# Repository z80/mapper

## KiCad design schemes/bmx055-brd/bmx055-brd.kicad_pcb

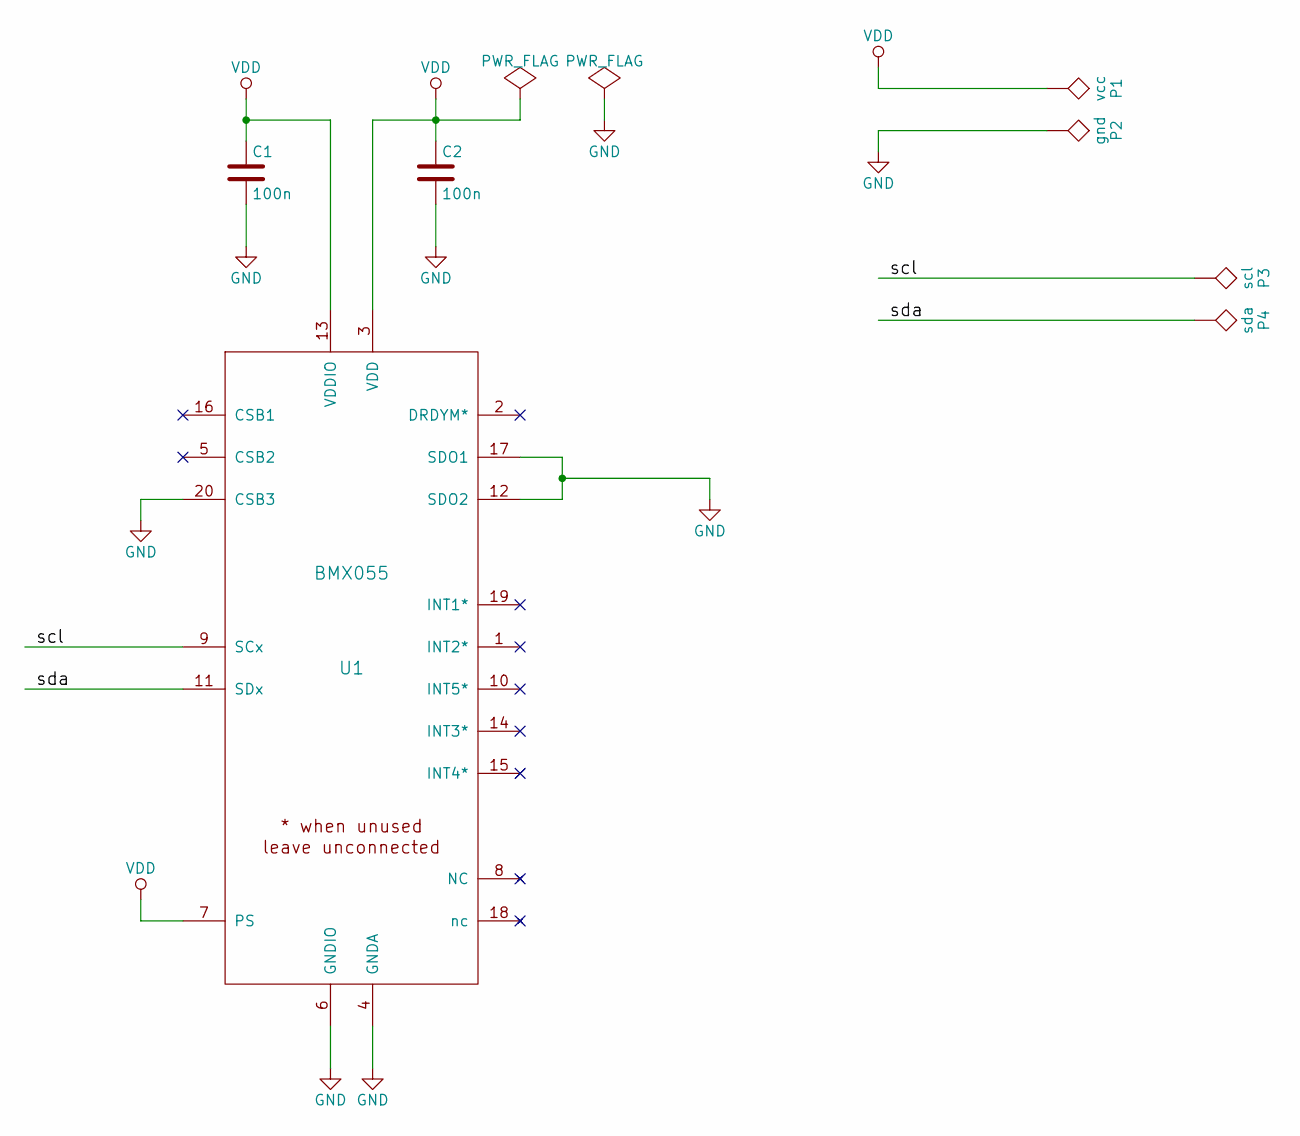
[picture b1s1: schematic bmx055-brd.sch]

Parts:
C1, C2: 100n; C_0805
P1: vcc; Measurement_Point_Round-SMD-Pad_Small
P2: gnd; Measurement_Point_Round-SMD-Pad_Small
P3: scl; Measurement_Point_Round-SMD-Pad_Small
P4: sda; Measurement_Point_Round-SMD-Pad_Small
U1: BMX055; bmx055-w

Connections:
/scl: P3.1, U1.9 (SCx)
/sda: P4.1, U1.11 (SDx)
GND: C1.2, C2.2, P2.1, U1.4 (GNDA), U1.6 (GNDIO), U1.12 (SDO2), U1.17 (SDO1), U1.20 (CSB3)
VDD: C1.1, C2.1, P1.1, U1.3 (VDD), U1.7 (PS), U1.13 (VDDIO)

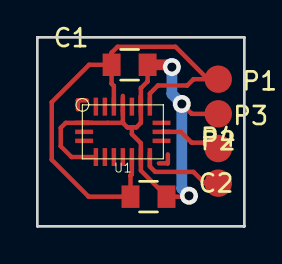
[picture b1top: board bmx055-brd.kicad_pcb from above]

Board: 2 copper layers, 11.5 x 10.5 mm, 7 parts (0 on the bottom side), 4 nets.

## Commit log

2015-09-07 The very first revision. Forgotten almost everything!!!!!
2015-09-15 Corners foundation works.
2015-10-15 Changing the algorithm...
2015-10-16 Modifying to make points to be tracked with screen positions and camera positions.
2015-10-24 Some recognition works.
2015-10-24 Made tests folder.
2015-10-24 ORB is much faster.
2015-10-30 Implemented a couple of functions.
2015-11-02 Point drawing works after disabling some modes...
2015-11-02 Debug information output.
2015-11-03 Filling points saving.
2015-11-04 Debugging positions.
2015-11-05 Tracking by features.
2015-11-05 Always track ref. frame.
2015-11-09 Checke by trying different combinations. It looks like geometry works this time :)
2015-11-11 This #$@ doesn't work in principle. It works only in model situations. But with real images I constantly get #$@ :((((((
2016-05-25 Added SVG chess board.
2016-05-25 Finding perspective transform.
2016-05-27 Retrieved perspective transform matrix via chessboard observation and meaning over time.
2016-05-28 Copied default example. Going to base detection on this example.
2016-05-29 Rectangles detection.
2016-05-29 Designing RF converion algorithms.
2016-05-31 Added cnc linraty and cnc cad.
2016-06-04 Implemented floor2vise and sample2Floor calibrations.
2016-06-06 Video flow estimation makes things much worse.
2016-06-08 Added end mill position visualization. To be debugged.
2016-06-08 Visualization doesn't work.
2016-06-08 More or less works.
2016-06-10 Testing stupid method...
2016-06-13 Added drives manipulation dialog.
2016-06-13 Added CAM.
2016-06-13 Made buildable in visual studio.
2016-06-14 It looks like it really turns mesh in the right way.
2016-06-14 Now cam-test does exactly what is needed. It picks face, colorates it and provides details.
2016-06-16 Edge selection doesn't find second triangle due to some reason.
2016-06-17 Edge selection with normal determination works.
2016-06-18 Removed unused code.
2016-06-20 Drop on face started working. Edge selection broke.
2016-06-20 Working on edge selection.
2016-06-21 Lagrange mulyipliers method works. Or at least it seems it works.
2016-06-21 Really no much difference with just least square method.
2016-06-21 Using SVD didnv provide with appropriate results. Transofrmation really is ortogonal. But it is obviously doesn't match data well.
2016-06-21 Started redesigning sample alignment.
2016-06-21 Experimenting with sample positioning.
2016-06-22 Edge alignment doesn't work.
2016-06-22 It looks like it works but it is necessary to provide at least 4 different edges to make it nontrivial.
2016-06-24 Will try to recode throuth jacobian.
2016-06-25 It seems like via jacobian it works!
2016-06-26 Removed unneeded fields.
2016-06-27 Adjusted floor to sample in accordance with accepted paradigm :)
2016-07-02 Right now it seems it works somehow. For now I have no more ideas how to improve it. One thing I don't uderstand 100% is why Jacobian determinant is 0 for already ortogonal matrix.
2016-07-04 Making points list displaying.
2016-07-09 Designing new approach...
2016-07-09 Prepared changes to work with points in front of edges.
2016-07-12 Works but precision is not quite promising.
2016-07-12 Adding rounding.
2016-07-12 Trying to boost up positioning.
2016-07-15 Added one definitely required step and one adjjustpemt to compile in Linux.
2016-07-15 Known squares method more or less works. Sometimes RF breaks strangely. It often happens during rotational movements.
2016-07-18 Modified positioning algorithm.
2016-07-27 Tested overwriting global new() and delete() operators.
2016-08-11 Fixed namespace error raised with new gcc aster OS upgrade.
2016-08-11 Studying problem.
2016-08-11 Studying saving to dedicated folders.
2016-08-12 Implemented copying linked list with cross references via old->new pair list.
2016-08-15 Tree serialization/deserialization.
2016-08-22 Added the most recent "micropython" and "pawn" versions just to have snapshots.
2016-09-12 Started BMX055 schematics.
2016-09-12 Making schematic for BMX055.
2016-09-13 Remade board for I2C mode and prepared for tonner transfer.
2016-10-18 Compiles but calculates state covariance in wrong way. It becomes negative. Probably it is caused by wrong W values.
2016-10-18 It looks like it works with 1 dimensional case.
2016-10-18 Fixed a little bit. Weigths calculation wasn't correct. Now works for two dimensions.
2016-10-18 Added acceleration. It immediately caused error double integration.
2016-10-18 Rearranged public and private fields within a class.
2016-10-18 Just experimenting with different conditions.
2016-10-20 PDFs concenring filtering.
2016-10-20 Splitted up prediction and correction steps.
2016-10-26 Experimenting with double sensing at different rates.
2016-11-26 Different derivations...
2016-11-27 In correction step used sigma points instead of their projections after transformation. It improved situation in 1D. As for 3D all is the same bad.
2016-11-28 It works for 1D now with custom weights.
2016-11-28 Engaged spinning. Still works...
2016-11-28 1D still works! Going to try external constant and see what happens.
2016-11-28 With external interference still works and measures it correctly!
2016-11-28 Started remaking 3D simulation.
2017-09-18 Docs
